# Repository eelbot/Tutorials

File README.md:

# Tutorials

This repository is meant to hold tutorials and projects
that are used for teaching and workshops. These are not meant
as a replacement for other resources. They are just meant as a
useful tool that I am incredibly familiar with to teach or help
with certain concepts. There is a lot of text in some of these
tutorials, and so if you spot a problem, please point it
out so I can fix it! 

## Python
I originally created the Python tutorial for two reasons. One,
because I really like the language, and two, because it would
be much easier to use than C in a programming challenge, and
I needed something to refer to if I was going to give
tutorials on it. A breakdown is below.
1. Introduction to syntax, math, and while loops
2. Introduction to arrays, strings, and for loops
3. String/Array manipulation, intro to other sequences
4. Intro to functions, input, and output

## C
The C language tutorial is intended as a quick review on
several aspects of syntax. It also provides a brief intro
to pointers.
1. Variables, operations, decisions, loops
2. Arrays, pointers, and strings
3. Input and output

## Arduino
This area is intended for all workshops for the Arduino. Still
a work in progress.

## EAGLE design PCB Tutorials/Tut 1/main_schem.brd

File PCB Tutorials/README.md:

# PCB Tutorials
These tutorials are focused on using the program EagleCAD to create PCB's. It will be updated periodically with more information, and tutorials. If you are just starting out, I recommend (and expect in my first tutorial) that you complete the Sparkfun guide to installing and setting up eagle, found here: [Sparkfun Eagle Tutorial](https://learn.sparkfun.com/tutorials/how-to-install-and-setup-eagle)

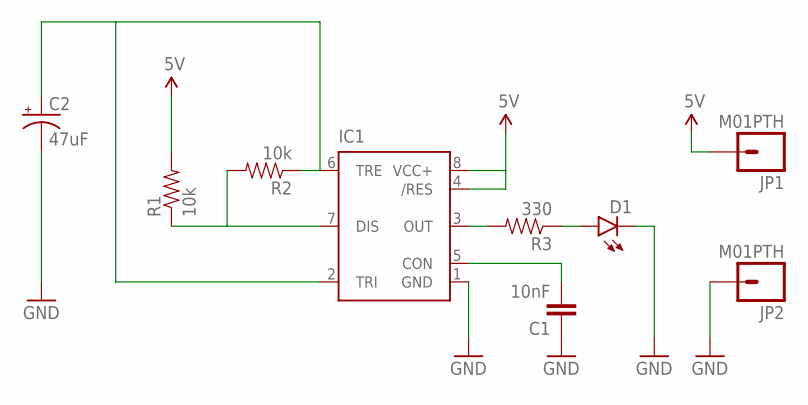
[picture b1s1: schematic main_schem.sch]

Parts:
C1: 10nF; CAP-PTH-SMALL
C2: 47uF; CPOL-RADIAL-10UF-25V
D1: LED5MM
IC1: NE555KIT; DIP08-KIT
JP1, JP2: M01PTH; 1X01
R1, R2: 10k; AXIAL-0.3
R3: 330; AXIAL-0.3

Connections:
5V: IC1.4 (/RES), IC1.8 (VCC+), JP1.1, R1.P$2 (2)
GND: C1.1, C2.2 (-), D1.K (C), IC1.1 (GND), JP2.1
unnamed: C1.2, IC1.5 (CON)
unnamed: IC1.7 (DIS), R1.P$1 (1), R2.P$2 (2)
unnamed: IC1.3 (OUT), R3.P$2 (2)
unnamed: C2.1 (+), IC1.2 (TRI), IC1.6 (TRE), R2.P$1 (1)
unnamed: D1.A, R3.P$1 (1)

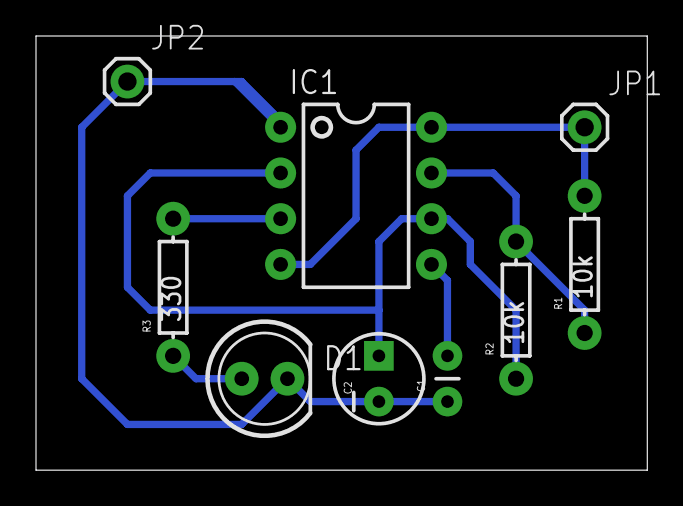
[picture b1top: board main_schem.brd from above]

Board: 2 copper layers, 34.0 x 24.1 mm, 9 parts (0 on the bottom side), 7 nets.

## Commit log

2015-08-13 Created this to seperate solutions and learning
2015-08-23 Updating and adding tutorials and READMEs
2015-09-16 Added Arduino tutorials and Python examples
2015-09-24 Added PCB tutorial
2015-10-01 Updated. Now contains gerber file generation.
2016-01-07 Updated ReadMe's
2016-01-26 Added Photoresistor and Pretend_Analog
2016-02-18 Updated wording

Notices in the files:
parts and their libraries:
SparkFun-Capacitors: Licensing: Creative Commons ShareAlike 4.0 International - https://creativecommons.org/licenses/by-sa/4.0
